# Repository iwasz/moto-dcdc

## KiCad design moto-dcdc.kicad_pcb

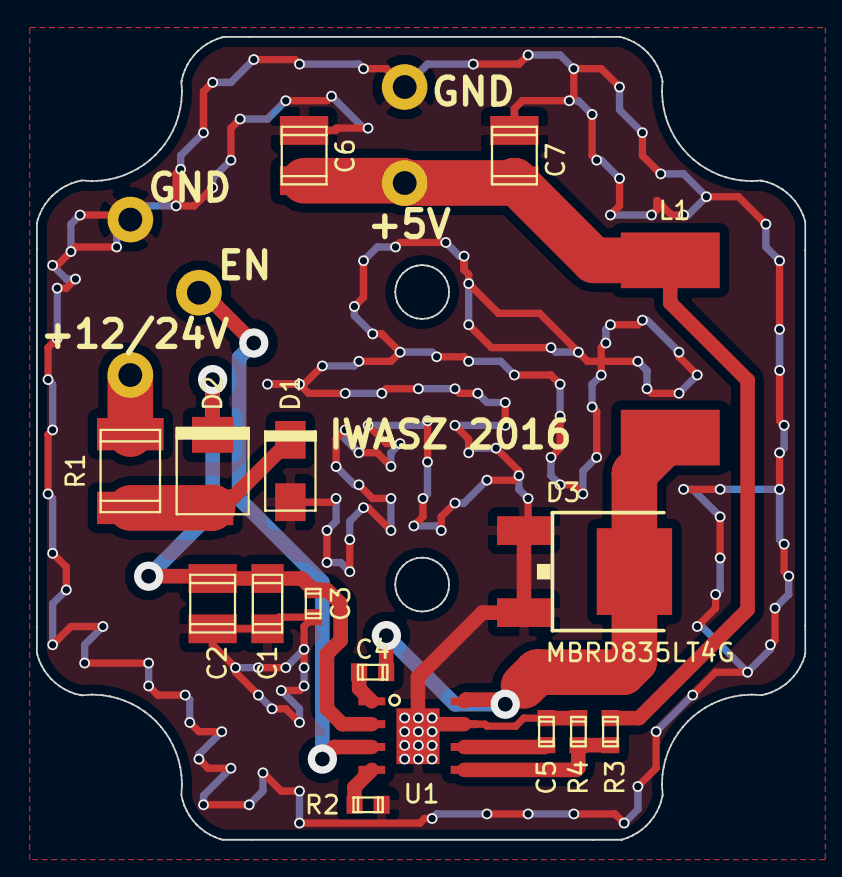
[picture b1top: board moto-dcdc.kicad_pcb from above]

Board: 2 copper layers, 42.7 x 44.6 mm, 21 parts (0 on the bottom side), 11 nets.

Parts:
C1: 4.7-10µF 50V X5R/X7R; c_1206
C2: 2.2µF 100V X7R; c_1210
C3: 100nF 50V; c_0603
C4: 100nF 16V X5R/X7R; c_0603
C5: 22nF; c_0603
C6, C7: 47µF 16V X7R; c_1210
D1: SMAJ33A; do214ac
D2: MBRS130L; do214aa-C1-A2
D3: MBRD835LT4G; DPAK-diode
L1: 8.2µH 7Arms 10Asat; 12.5x12.5_inductor
P1, P2, P3, P4, P5: CONN_01X01; PAD-01
R1: 12V 3A/6A; c_1812
R2: 49.9k 1%; r_0603
R3: 56.6k 1%; r_0603
R4: 10k 1%; r_0603
U1: LMR14050; HSOIC_8_powerpad

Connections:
+5V: C6.1, C7.1, L1.2, P4.1, R3.1
+12V: P2.1, R1.2
GND: C1.1, C2.1, C3.1, C5.1, C6.2, C7.2, D1.1, D3.2, P1.1, P5.1, R2.2, R4.2, U1.7
unnamed: C1.2, C2.2, C3.2, D2.1, U1.2
unnamed: C4.1, D3.1, L1.1, U1.8
unnamed: C4.2, U1.1
unnamed: C5.2, U1.6
unnamed: D1.2, D2.2, R1.1
unnamed: P3.1, U1.3
unnamed: R2.1, U1.4
unnamed: R3.2, R4.1, U1.5

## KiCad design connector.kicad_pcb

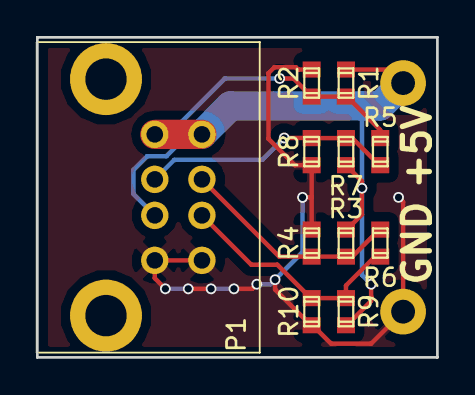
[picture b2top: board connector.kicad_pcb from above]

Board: 2 copper layers, 22.2 x 17.8 mm, 13 parts (0 on the bottom side), 6 nets.

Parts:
P1: CONN_01X08; amphenol-MUSBC11130
P2, P3: CONN_01X01; PAD-01
R1, R2, R3, R4, R5, R6, R7, R8, R9, R10: R; r_0603

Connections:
+5V: P1.1, P1.5, P3.1, R1.2, R3.2, R7.2, R9.2
GND: P1.4, P1.8, P2.1, R2.1, R4.1, R8.1, R10.1
unnamed: P1.2, R3.1, R4.2, R6.1
unnamed: P1.3, R6.2, R9.1, R10.2
unnamed: P1.6, R5.2, R7.1, R8.2
unnamed: P1.7, R1.1, R2.2, R5.1

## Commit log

2016-04-11 Connector
2016-07-01 Gerbers
